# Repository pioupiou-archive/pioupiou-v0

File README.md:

pioupiou-v0
===========

Fichiers sources pour la balise Pioupiou version 0

Les fichiers de CAO (schéma et PCB) sont à utiliser avec le logiciel Kicad, gratuit (et Grenoblois !). Disponible pour Windows, Mac et Linux sur http://www.kicad-pcb.org/

Ce « brouillon » a été mis à la retraite après avoir rempli sa mission. Nous pouvons maintenant nous appuyer sur cette expérience pour mettre au point Pioupiou version 1. https://open.pioupiou.fr/Pioupiou_v1

## BUGS :
Il y a deux bugs à corriger sur cette version :
* Il faut enlever le plan de masse sous les connecteurs des batteries, sinon risque de court-circuit.
* Il faut ajouter une TVS ainsi qu'une self de 10nH en parallèle entre l'antenne et la masse. (protection électricité statique des orages)

## License

Copyright (c) 2015 Bac Plus Zéro SAS

Copyright (c) 2016 Altostratus SA

Copyright (c) 2021 OpenWindMap SCIC SA and contributors

**Permission is granted to anyone to use this Material for any purpose, including commercial applications, and to alter it and redistribute it freely, subject to the following restrictions:**

**ATTRIBUTION:** You must give appropriate credit, provide a link to the license, and indicate if changes were made. You may do so in any reasonable manner, but not in any way that suggests the licensor endorses you or your use.

**SHARE-ALIKE:** If you remix, transform, or build upon the Material, you must distribute your contributions under the same license as the original. You must include a copy of this License with every copy of this Material or modified version of this Material You distribute or otherwise make available.

**OBLIGATION TO SHARE WITHIN THE OPENWINDMAP NETWORK:** If you use this Material or a modified version of this Material to build a product that collects environmental data, this data must be published within the OpenWindMap network. You must not intentionally degrade the quality of the data, reduce the accuracy of its geolocation or delay its dissemination.

**OPEN-DATA:** If you use this Material or a modified version of this Material to build a product that collects environmental data, this data should be published under an Open-Data license. The chosen license must allow free reuse and redistribution, including from commercial entities and for commercial use. The choosen license must either be compliant with the [Open Definition](https://opendefinition.org/od/2.1/en/) or receive approval from OpenWindMap's board. You are allowed to offer a version of this data under any other license of your choice (including non-free licenses), as long as you also provide an identical version of this data under an Open-Data license as defined in this paragraph.

**DISCLAIMER OF WARRANTY/LIMITATION OF REMEDIES:** OpenWindMap and its contributors have no obligation to support this Material. OpenWindMap and its contributors are providing this Material "AS IS", with no express or implied warranties of any kind, including, but not limited to, any implied warranties of merchantability or fitness for any particular purpose or warranties against infringement of any proprietary rights of a third party.

**OpenWindMap and its contributors will not be liable for any consequential, incidental, or special damages, or any other relief, or for any claim by any third party, arising from your use of this Material.**

For the avoidance of doubt, OpenWindMap may offer this Material under separate terms or conditions or stop distributing this Material at any time; however, doing so will not terminate this License.

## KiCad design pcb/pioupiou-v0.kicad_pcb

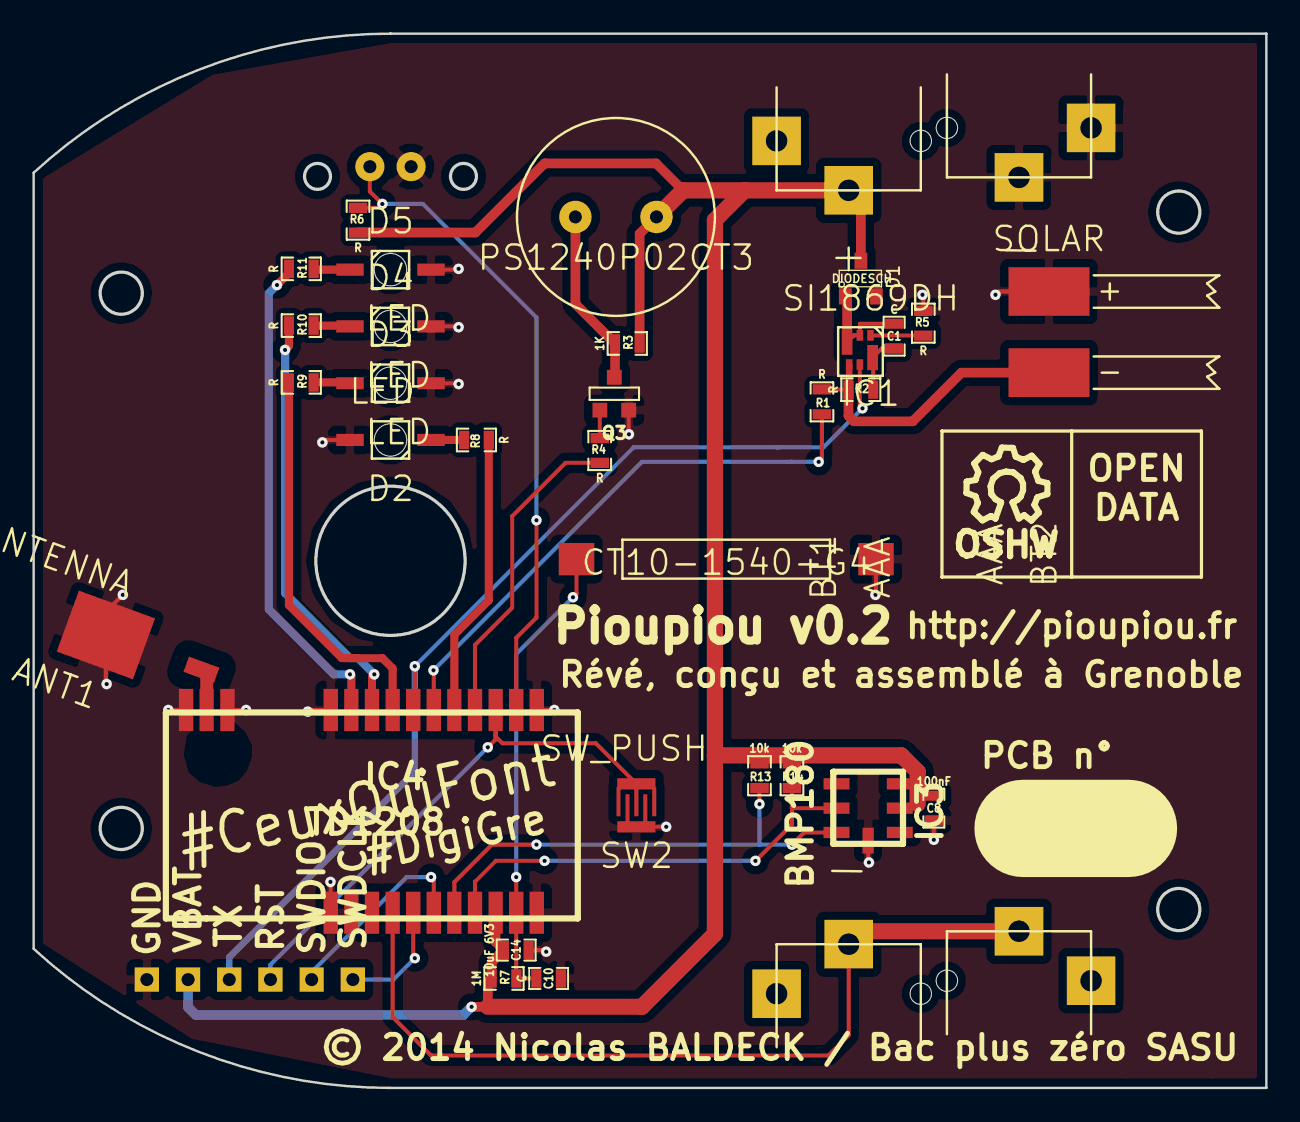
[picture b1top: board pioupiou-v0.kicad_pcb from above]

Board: 2 copper layers, 76.0 x 65.0 mm, 41 parts (1 on the bottom side), 28 nets.

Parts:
ANT1: ANTENNA; RG178_SOLDER
BT1, BT2: AAA; AAA_KEYSTONE
C1, C10: C; SM0603_Capa
C8: 100nF; SM0603_Capa
C14: 10uF 6V3; SM0603_Capa
D1: DIODESCH; SOT23
D2, D3, D4, D5: LED; LED_2mm_GW
GND: CONN_1; Measurement_Point_Square-TH_Small
IC1: SI1869DH; Si1869DH
IC3: BMP180
IC4: TD1208
P1: SOLAR; SOLAR_WIRE
Q1: OPTO_NPN; PHOTOTRANS
Q3: NPN; SOT23EBC
R1, R2, R4, R5, R6, R8, R9, R10, R11: R; SM0603_Resistor
R3: 1K; SM0603_Resistor
R7: 1M; SM0603_Resistor
R13, R14: 10k; SM0603_Resistor
RST: CONN_1; Measurement_Point_Square-TH_Small
SP1: PS1240P02CT3
SW1: CT10-1540-G4
SW2: SW_PUSH; SW_CARBON
SWDCLK: CONN_1; Measurement_Point_Square-TH_Small
SWDIO: CONN_1; Measurement_Point_Square-TH_Small
SYM: Symbol_OSHW-Logo_SilkScreen_07Jul2012
TX: CONN_1; Measurement_Point_Square-TH_Small
VBAT: CONN_1; Measurement_Point_Square-TH_Small

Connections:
/BAT_SENSE: BT1.2, BT2.1, IC4.4
/BUZZ: IC4.15, R4.1
/LED_DIR1: IC4.16, R8.1
/LED_DIR2: IC4.19, R9.1
/LED_DIR3: IC4.20, R10.1
/LED_DIR4: IC4.21, R11.1
/OPTO_SIGNAL: IC4.13, Q1.3, R6.2
/REED_SIGNAL: C10.1, IC4.10, R7.2, SW1.1
/RST: IC4.14, RST.1, SW2.1
/SCL: IC3.5, IC4.8, R14.2
/SDA: IC3.6, IC4.7, R13.2
/SOLAR_SENSE: IC4.17, R1.2
/SOLAR_SW: IC1.5, IC4.18, TX.1
/SWDCLK: IC4.5, SWDCLK.1
/SWDIO: IC4.6, SWDIO.1
/VBAT: BT1.1, C8.1, C14.1, D1.3, IC3.2, IC3.3, IC4.9, R3.2, R6.1, R7.1, R13.1, R14.1, SP1.1, VBAT.1
GND: ANT1.2, BT2.2, C8.2, C10.2, C14.2, D2.2, D3.2, D4.2, D5.2, GND.1, IC3.7, IC4.1, IC4.2, IC4.11, IC4.12, IC4.22, IC4.23, IC4.25, P1.2, Q1.1, Q3.1, R5.2, SW1.2, SW2.2
unnamed: ANT1.1, IC4.24
unnamed: IC1.1, R5.1
unnamed: C1.2, IC1.6, R2.2
unnamed: IC1.4, P1.1, R1.1, R2.1
unnamed: C1.1, D1.1, IC1.2, IC1.3
unnamed: Q3.2, R4.2
unnamed: Q3.3, R3.1, SP1.2
unnamed: D2.1, R8.2
unnamed: D5.1, R11.2
unnamed: D4.1, R10.2
unnamed: D3.1, R9.2

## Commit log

2014-10-03 Upload vers github
2014-10-03 liste des bugs
2021-03-11 add picture

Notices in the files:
pcb/pioupiou-v0.kicad_pcb:
© 2014 Nicolas BALDECK / Bac plus zéro SASU
